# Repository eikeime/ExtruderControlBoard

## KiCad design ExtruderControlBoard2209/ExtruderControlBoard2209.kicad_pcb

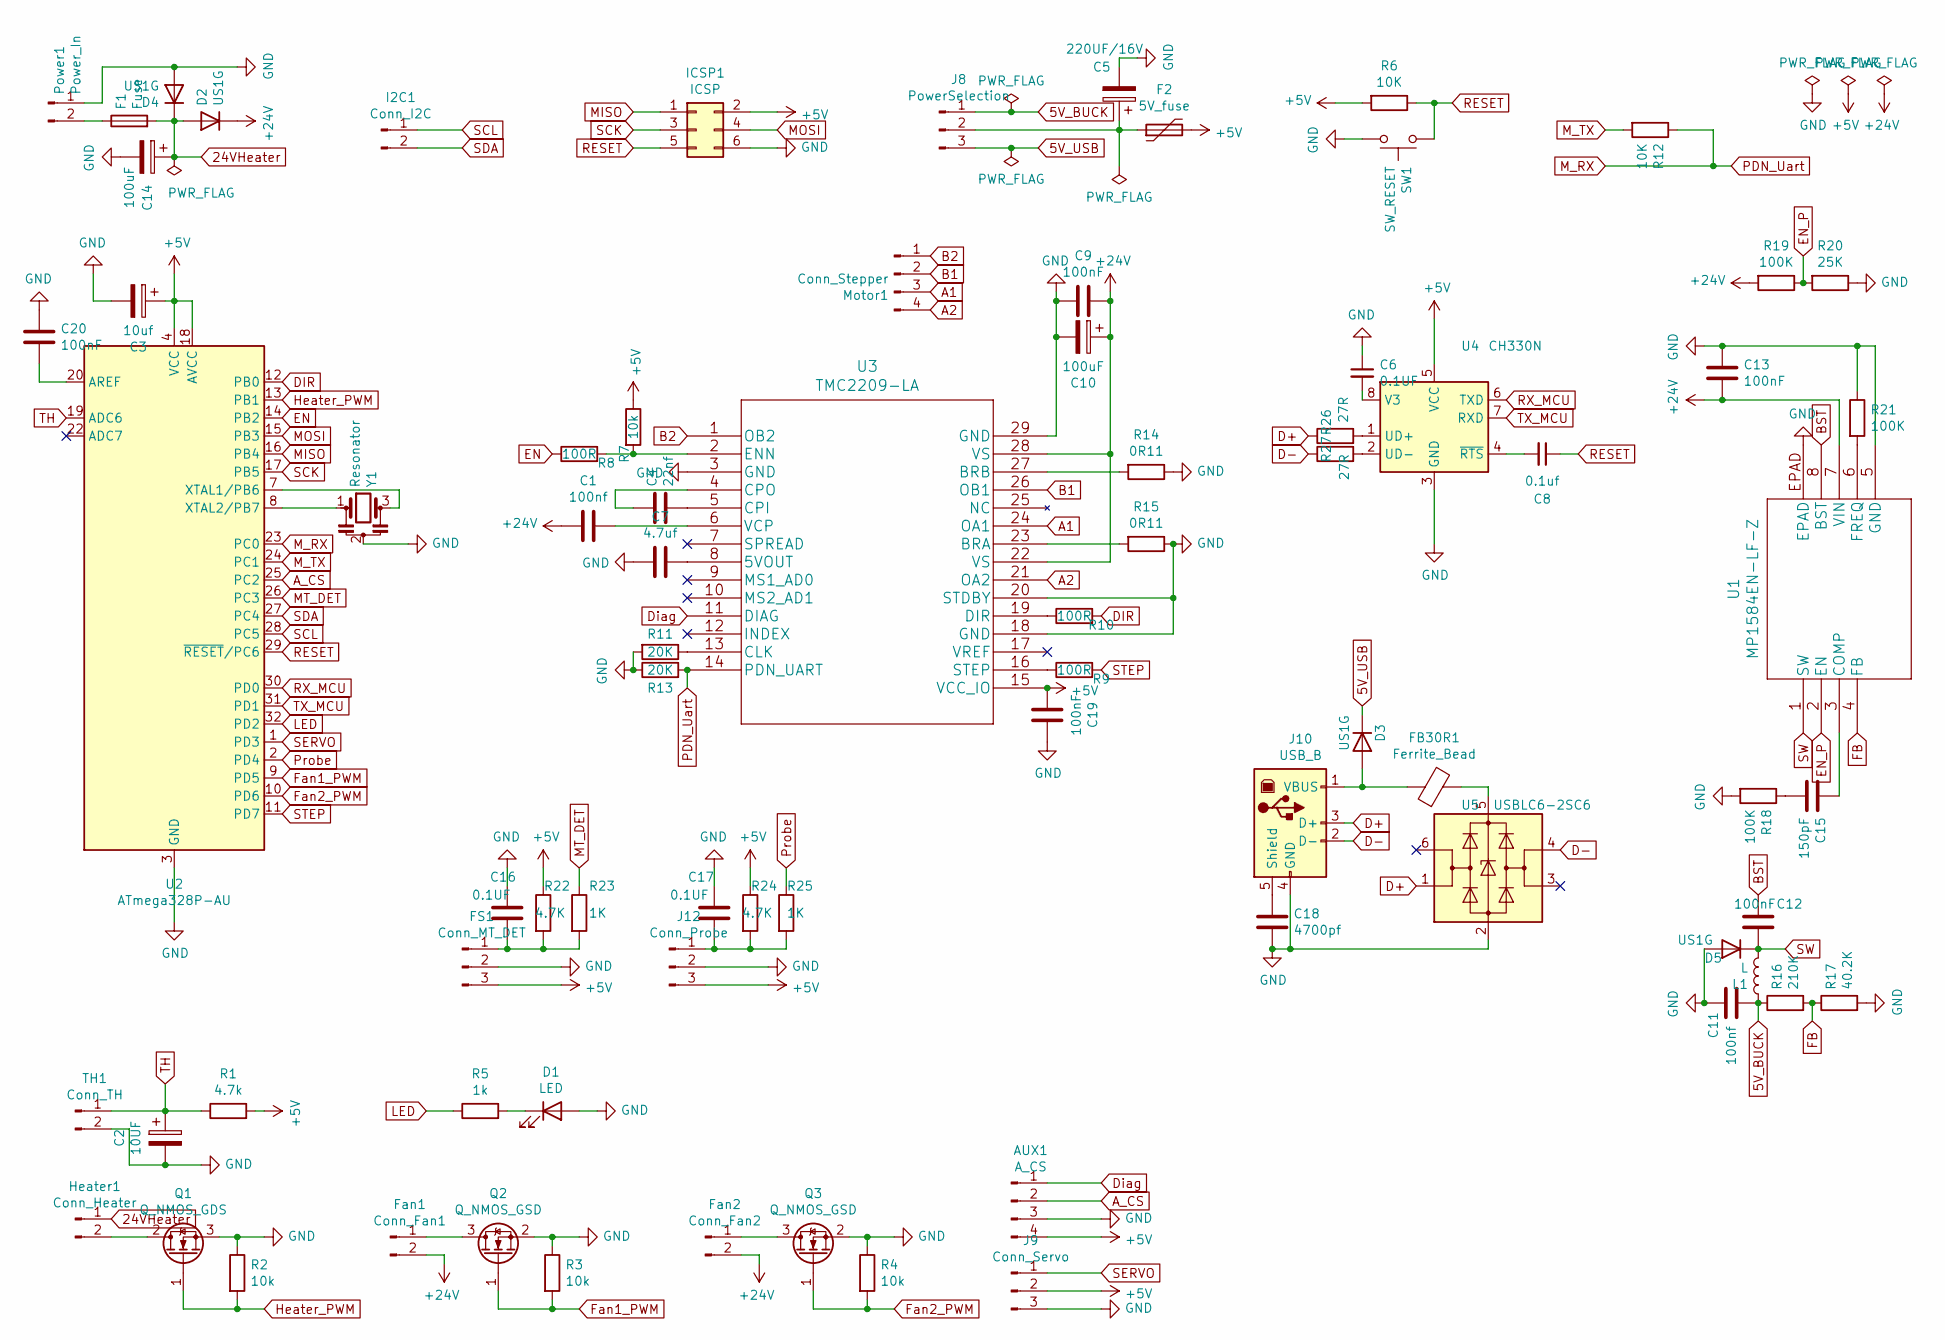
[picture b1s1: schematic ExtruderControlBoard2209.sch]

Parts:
AUX1: A_CS; PinHeader_1x04_P2.54mm_Vertical
C1, C11: 100nf; C_0805_2012Metric_Pad1.18x1.45mm_HandSolder
C2: 10UF; C_0805_2012Metric_Pad1.18x1.45mm_HandSolder
C3: 10uf; C_0805_2012Metric_Pad1.18x1.45mm_HandSolder
C4: 22nf; C_0805_2012Metric_Pad1.18x1.45mm_HandSolder
C5: 220UF/16V; CP_Elec_4x5.4
C6, C16, C17: 0.1UF; C_0805_2012Metric_Pad1.18x1.45mm_HandSolder
C7: 4.7uf; C_0805_2012Metric_Pad1.18x1.45mm_HandSolder
C8: 0.1uf; C_0805_2012Metric_Pad1.18x1.45mm_HandSolder
C9, C12, C13, C19, C20: 100nF; C_0805_2012Metric_Pad1.18x1.45mm_HandSolder
C10, C14: 100uF; CP_Elec_6.3x7.7
C15: 150pF; C_0805_2012Metric_Pad1.18x1.45mm_HandSolder
C18: 4700pf; C_0805_2012Metric_Pad1.18x1.45mm_HandSolder
D1: LED; LED_0805_2012Metric_Pad1.15x1.40mm_HandSolder_holeInside
D2, D3, D4, D5: US1G; D_SMA_Handsoldering
F1: Fuse; Fuse_2816_7142Metric_Pad3.20x4.45mm_HandSolder
F2: 5V_fuse; Fuse_1812_4532Metric_Pad1.30x3.40mm_HandSolder
FB30R1: Ferrite_Bead; L_0805_2012Metric_Pad1.15x1.40mm_HandSolder
FS1: Conn_MT_DET; JST_XH_B3B-XH-A_1x03_P2.50mm_Vertical
Fan1: Conn_Fan1; JST_XH_B2B-XH-A_1x02_P2.50mm_Vertical
Fan2: Conn_Fan2; JST_XH_B2B-XH-A_1x02_P2.50mm_Vertical
Heater1: Conn_Heater; TerminalBlock_Phoenix_MKDS-1,5-2_1x02_P5.00mm_Horizontal
I2C1: Conn_I2C; PinHeader_1x02_P2.54mm_Vertical
ICSP1: ICSP; PinHeader_2x03_P2.54mm_Vertical
J8: PowerSelection; PinHeader_1x03_P2.54mm_Vertical
J9: Conn_Servo; PinHeader_1x03_P2.54mm_Vertical
J10: USB_B; USB_B_OST_USB-B1HSxx_Horizontal
J12: Conn_Probe; PinHeader_1x03_P2.54mm_Vertical
L1: L; L_Taiyo-Yuden_NR-60xx_HandSoldering
Motor1: Conn_Stepper; JST_XH_B4B-XH-A_1x04_P2.50mm_Vertical
Power1: Power_In; TerminalBlock_Phoenix_MKDS-1,5-2_1x02_P5.00mm_Horizontal
Q1: Q_NMOS_GDS; TO-252-2
Q2, Q3: Q_NMOS_GSD; SOT-23_Handsoldering
R1: 4.7k; R_0805_2012Metric_Pad1.20x1.40mm_HandSolder
R2, R3, R4, R7: 10k; R_0805_2012Metric_Pad1.20x1.40mm_HandSolder
R5: 1k; R_0805_2012Metric_Pad1.20x1.40mm_HandSolder
R6, R12: 10K; R_0805_2012Metric_Pad1.20x1.40mm_HandSolder
R8, R9, R10: 100R; R_0805_2012Metric_Pad1.20x1.40mm_HandSolder
R11, R13: 20K; R_0805_2012Metric_Pad1.20x1.40mm_HandSolder
R14, R15: 0R11; R_1206_3216Metric_Pad1.30x1.75mm_HandSolder
R16: 210K; R_0805_2012Metric_Pad1.20x1.40mm_HandSolder
R17: 40.2K; R_0805_2012Metric_Pad1.20x1.40mm_HandSolder
R18, R19, R21: 100K; R_0805_2012Metric_Pad1.20x1.40mm_HandSolder
R20: 25K; R_0805_2012Metric_Pad1.20x1.40mm_HandSolder
R22, R24: 4.7K; R_0805_2012Metric_Pad1.20x1.40mm_HandSolder
R23, R25: 1K; R_0805_2012Metric_Pad1.20x1.40mm_HandSolder
R26, R27: 27R; R_0805_2012Metric_Pad1.20x1.40mm_HandSolder
SW1: SW_RESET; SW_SPST_FSMSM
TH1: Conn_TH; JST_XH_B2B-XH-A_1x02_P2.50mm_Vertical
U1: MP1584EN-LF-Z
U2: ATmega328P-AU; TQFP-32_7x7mm_P0.8mm
U3: TMC2209-LA
U4: CH330N; SOIC-8_3.9x4.9mm_P1.27mm
U5: USBLC6-2SC6; SOT-23-6
Y1: Resonator; Resonator_SMD_muRata_CSTxExxV-3Pin_3.0x1.1mm_HandSoldering

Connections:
5V_BUCK: C11.2, J8.1, L1.1, R16.1
5V_USB: D3.1 (K), J8.3
24VHeater: C14.1, D2.2 (A), D4.1 (K), F1.2, Heater1.1
+5V: AUX1.4, C3.1, C19.2, F2.2, FS1.3, ICSP1.2, J9.2, J12.3, R1.2, R6.2, R7.1, R22.1, R24.1, U2.4 (VCC), U2.6 (VCC), U2.18 (AVCC), U3.15 (VCC_IO), U4.5 (VCC)
+24V: C1.2, C9.1, C10.1, C13.2, D2.1 (K), Fan1.2, Fan2.2, R19.2, U1.7 (VIN), U3.22 (VS), U3.28 (VS)
A1: Motor1.3, U3.24 (OA1)
A2: Motor1.4, U3.21 (OA2)
A_CS: AUX1.2, U2.25 (PC2)
B1: Motor1.2, U3.26 (OB1)
B2: Motor1.1, U3.1 (OB2)
BST: C12.2, U1.8 (BST)
D+: J10.3 (D+), R26.1, U5.1 (I/O1)
D-: J10.2 (D-), R27.1, U5.4 (I/O2)
DIR: R10.2, U2.12 (PB0)
Diag: AUX1.1, U3.11 (DIAG)
EN: R8.1, U2.14 (PB2)
EN_P: R19.1, R20.2, U1.2 (EN)
FB: R16.2, R17.1, U1.4 (FB)
Fan1_PWM: Q2.1 (G), R3.2, U2.9 (PD5)
Fan2_PWM: Q3.1 (G), R4.2, U2.10 (PD6)
GND: AUX1.3, C2.2, C3.2, C5.2, C6.1, C7.2, C9.2, C10.2, C11.1, C13.1, C14.2, C16.1, C17.1, C18.2, C19.1, C20.1, D1.2 (A), D4.2 (A), D5.2 (A), FS1.2, ICSP1.6, J9.3, J10.4 (GND), J12.2, Power1.1, Q1.3 (S), Q2.2 (S), Q3.2 (S), R2.1, R3.1, R4.1, R11.2, R13.1, R14.1, R15.1, R17.2, R18.2, R20.1, R21.1, SW1.2, TH1.2, U1.5 (GND), U1.EPAD, U2.3 (GND), U2.5 (GND), U2.21 (GND), U3.3 (GND), U3.18 (GND), U3.20 (STDBY), U3.29 (GND), U4.3 (GND), U5.2 (GND), Y1.2
Heater_PWM: Q1.1 (G), R2.2, U2.13 (PB1)
LED: R5.1, U2.32 (PD2)
MISO: ICSP1.1, U2.16 (PB4)
MOSI: ICSP1.4, U2.15 (PB3)
MT_DET: R23.1, U2.26 (PC3)
M_RX: R12.1, R13.2, U2.23 (PC0), U3.14 (PDN_UART)
M_TX: R12.2, U2.24 (PC1)
unnamed: C1.1, U3.6 (VCP)
unnamed: C4.1, U3.4 (CPO)
unnamed: C4.2, U3.5 (CPI)
unnamed: C5.1, F2.1, J8.2
unnamed: C6.2, U4.8 (V3)
unnamed: C7.1, U3.8 (5VOUT)
unnamed: C8.2, U4.4 (~RTS)
unnamed: C15.1, U1.3 (COMP)
unnamed: C15.2, R18.1
unnamed: C16.2, FS1.1, R22.2, R23.2
unnamed: C17.2, J12.1, R24.2, R25.2
unnamed: C18.1, J10.5 (Shield)
unnamed: C20.2, U2.20 (AREF)
unnamed: D1.1 (K), R5.2
unnamed: D3.2 (A), FB30R1.1, J10.1 (VBUS)
unnamed: F1.1, Power1.2
unnamed: FB30R1.2, U5.5 (VBUS)
unnamed: Fan1.1, Q2.3 (D)
unnamed: Fan2.1, Q3.3 (D)
unnamed: Heater1.2, Q1.2 (D)
unnamed: R7.2, R8.2, U3.2 (ENN)
unnamed: R9.1, U3.16 (STEP)
unnamed: R10.1, U3.19 (DIR)
unnamed: R11.1, U3.13 (CLK)
unnamed: R14.2, U3.27 (BRB)
unnamed: R15.2, U3.23 (BRA)
unnamed: R21.2, U1.6 (FREQ)
unnamed: R26.2, U4.1 (UD+)
unnamed: R27.2, U4.2 (UD-)
unnamed: U2.7 (XTAL1/PB6), Y1.3
unnamed: U2.8 (XTAL2/PB7), Y1.1
Probe: R25.1, U2.2 (PD4)
RESET: C8.1, ICSP1.5, R6.1, SW1.1, U2.29 (~RESET~/PC6)
RX_MCU: U2.30 (PD0), U4.6 (TXD)
SCK: ICSP1.3, U2.17 (PB5)
SCL: I2C1.1, U2.28 (PC5)
SDA: I2C1.2, U2.27 (PC4)
SERVO: J9.1, U2.1 (PD3)
STEP: R9.2, U2.11 (PD7)
SW: C12.1, D5.1 (K), L1.2, U1.1 (SW)
TH: C2.1, R1.1, TH1.1, U2.19 (ADC6)
TX_MCU: U2.31 (PD1), U4.7 (RXD)

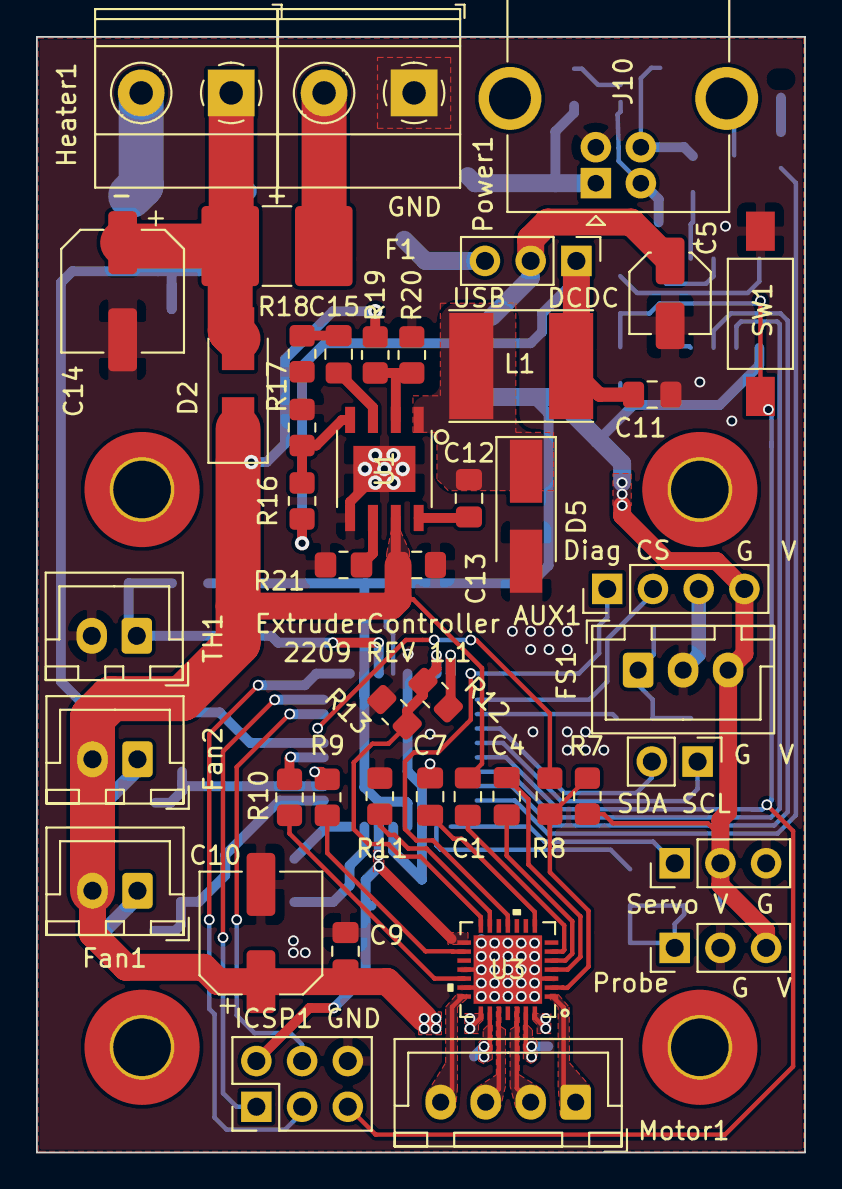
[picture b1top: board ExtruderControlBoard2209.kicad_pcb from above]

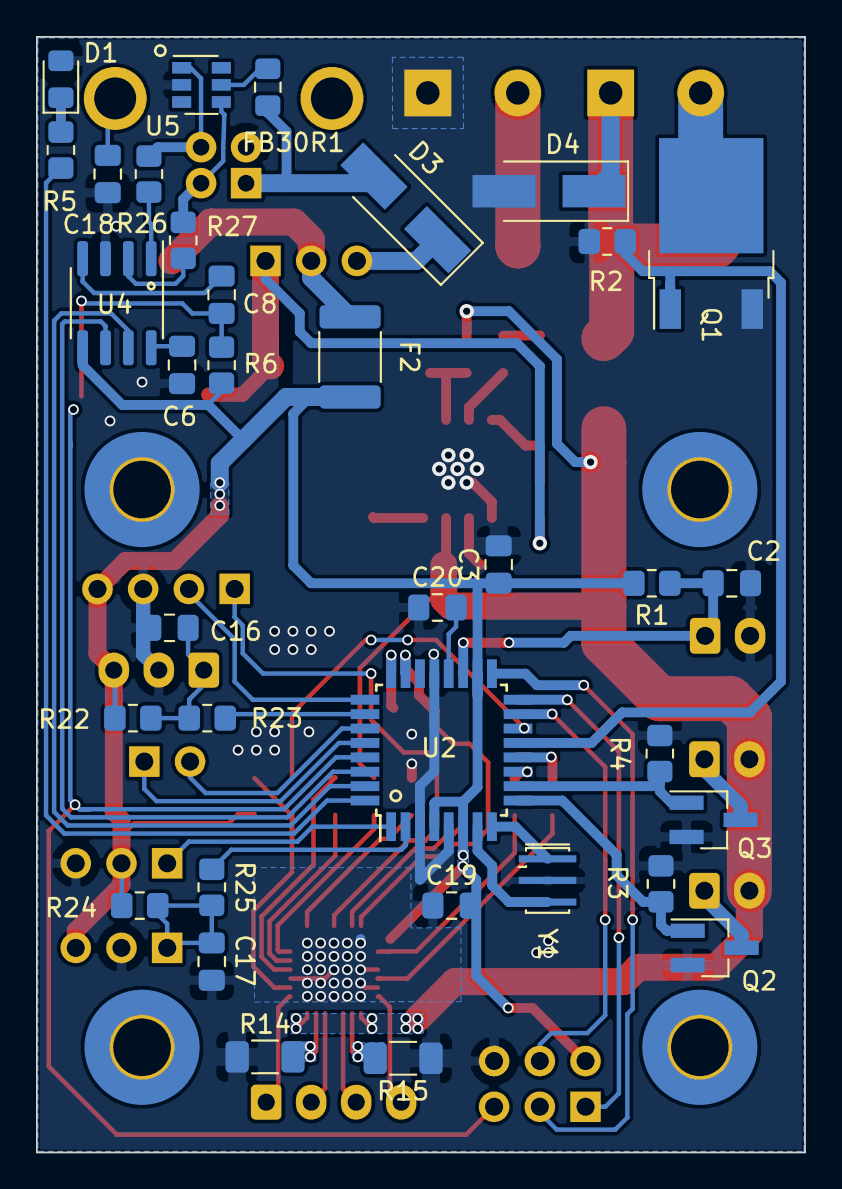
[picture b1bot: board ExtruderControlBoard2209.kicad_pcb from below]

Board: 2 copper layers, 42.7 x 62.0 mm, 80 parts (35 on the bottom side), 70 nets.

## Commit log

2021-11-16 intergreted tmc2209 board first version 2209_v1
2021-11-26 emifix
2022-07-10 minor optimization

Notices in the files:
parts and their libraries:
Copyright 2021 Accelerated Designs. All rights reserved.
